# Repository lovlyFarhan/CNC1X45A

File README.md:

CNC1X45A
========

Stepper motor driver based on TB6600

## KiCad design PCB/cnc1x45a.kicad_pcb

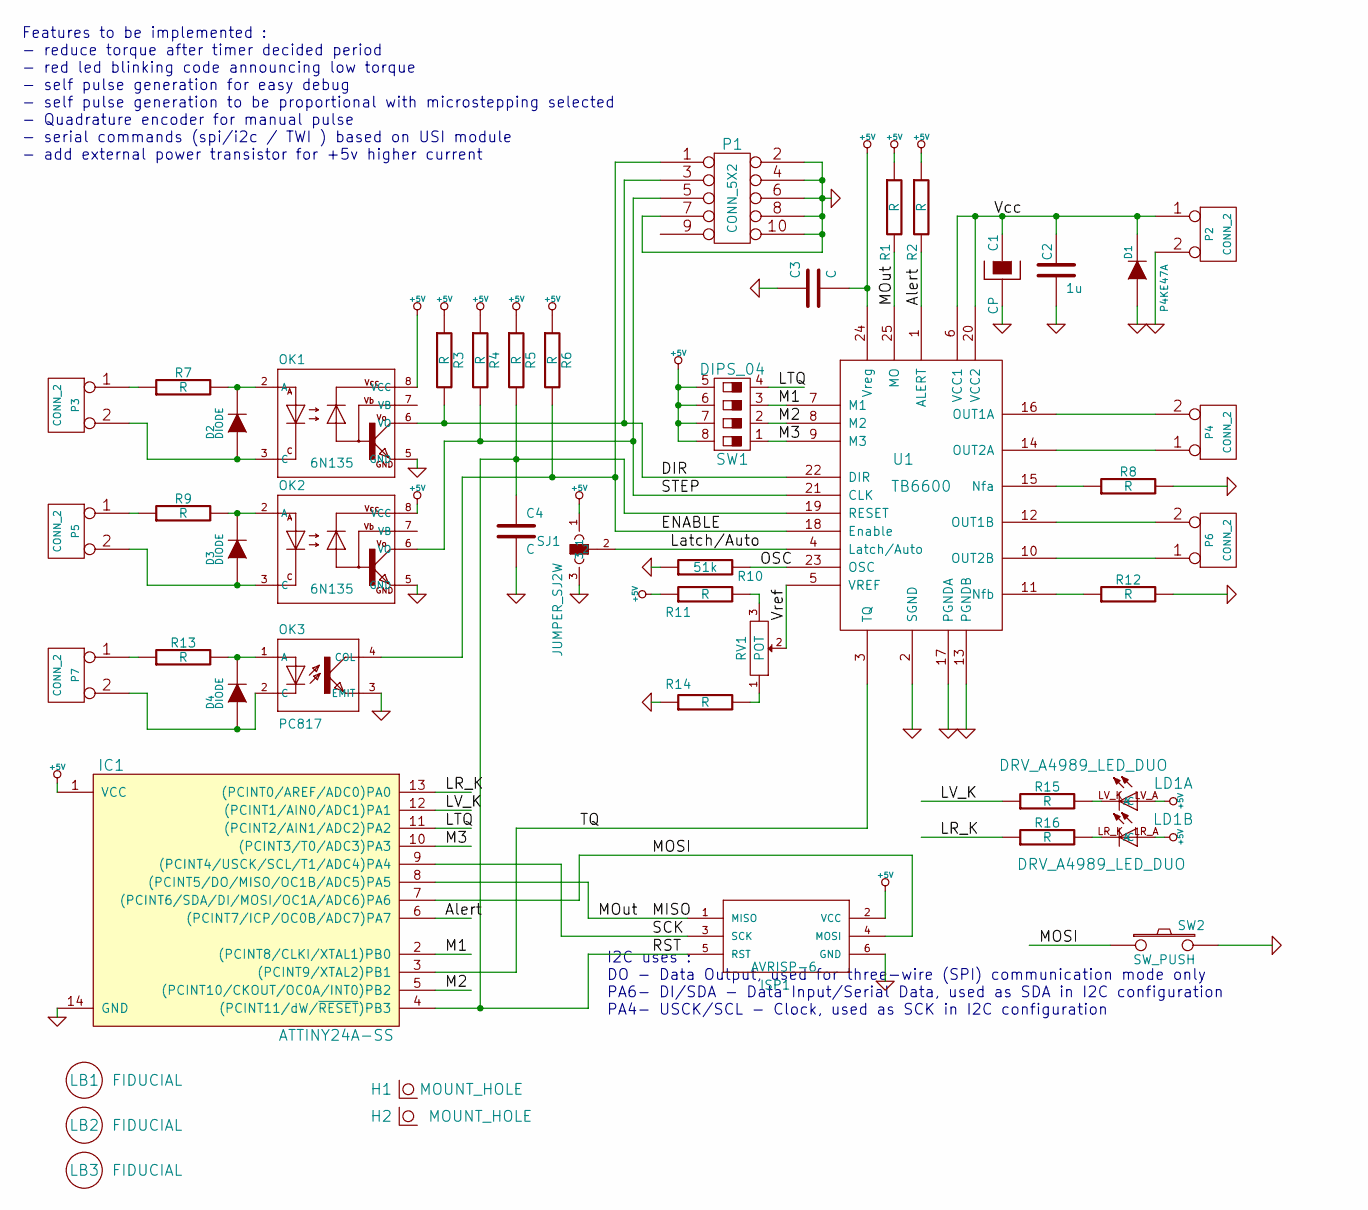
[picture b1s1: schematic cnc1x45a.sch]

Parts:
C1: CP
C2: 1u; SM1206
C3, C4: C
D1: P4KE47A
D2, D3, D4: DIODE
H1, H2: MOUNT_HOLE
IC1: ATTINY24A-SS; SO14
ISP1: AVRISP-6; adafruit-AVRISP
LB1, LB2, LB3: FIDUCIAL
LD1: DRV_A4989_LED_DUO
OK1, OK2: 6N135; optocoupler-2-DIL08
OK3: PC817; optocoupler-2-DIL04
P1: CONN_5X2
P2, P3, P4, P5, P6, P7: CONN_2
R1, R2, R3, R4, R5, R6, R7, R8, R9, R11, R12, R13, R14, R15, R16: R
R10: 51k
RV1: POT
SJ1: JUMPER_SJ2W; olimex-JUMPER_SJ_2
SW1: DIPS_04
SW2: SW_PUSH
U1: TB6600

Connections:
+5V: C3.2, IC1.1 (VCC), ISP1.2 (VCC), LD1.LR_A (A), LD1.LV_A (A), OK1.8 (VCC), OK2.8 (VCC), R1.1, R2.1, R3.1, R4.1, R5.1, R6.1, R11.1, SJ1.1, SW1.5, SW1.6, SW1.7, SW1.8, U1.24 (Vreg)
/Alert: IC1.6 ((PCINT7/ICP/OC0B/ADC7)PA7), R2.2, U1.1 (ALERT)
/DIR: OK1.6 (VO), P1.3, R3.2, U1.22 (DIR)
/ENABLE: OK3.4 (COL), P1.1, R6.2, U1.18 (Enable)
/LR_K: IC1.13 ((PCINT0/AREF/ADC0)PA0), R16.1
/LTQ: IC1.11 ((PCINT2/AIN1/ADC2)PA2), SW1.4
/LV_K: IC1.12 ((PCINT1/AIN0/ADC1)PA1), R15.1
/Latch/Auto: SJ1.2, U1.4 (Latch/Auto)
/M1: IC1.2 ((PCINT8/CLKI/XTAL1)PB0), SW1.3, U1.7 (M1)
/M2: IC1.5 ((PCINT10/CKOUT/OC0A/INT0)PB2), SW1.2, U1.8 (M2)
/M3: IC1.10 ((PCINT3/T0/ADC3)PA3), SW1.1, U1.9 (M3)
/MISO: IC1.8 ((PCINT5/DO/MISO/OC1B/ADC5)PA5), ISP1.1 (MISO), R1.2, U1.25 (MO)
/MOSI: IC1.7 ((PCINT6/SDA/DI/MOSI/OC1A/ADC6)PA6), ISP1.4 (MOSI), SW2.1
/OSC: R10.2, U1.23 (OSC)
/RST: C4.1, IC1.4 ((PCINT11/dW/~RESET~)PB3), ISP1.5 (RST), R5.2, U1.19 (RESET)
/SCK: IC1.9 ((PCINT4/USCK/SCL/T1/ADC4)PA4), ISP1.3 (SCK)
/STEP: OK2.6 (VO), P1.5, R4.2, U1.21 (CLK)
/TQ: IC1.3 ((PCINT9/XTAL2)PB1), U1.3 (TQ)
/Vcc: C1.1, C2.1, D1.2 (K), P2.1, U1.6 (VCC1), U1.20 (VCC2)
/Vref: RV1.2, U1.5 (VREF)
GND: C1.2, C2.2, C3.1, C4.2, D1.1 (A), IC1.14 (GND), ISP1.6 (GND), OK1.5 (GND), OK2.5 (GND), OK3.3 (EMIT), P1.2, P1.4, P1.6, P1.7, P1.8, P1.10, P2.2 (PM), R8.2, R10.1, R12.2, R14.1, SJ1.3, SW2.2, U1.2 (SGND), U1.13 (PGNDB), U1.17 (PGNDA)
unnamed: P5.1, R9.1
unnamed: D3.2 (K), OK2.2 (A), R9.2
unnamed: LD1.LR_K (C), R16.2
unnamed: LD1.LV_K (C), R15.2
unnamed: D3.1 (A), OK2.3 (C), P5.2 (PM)
unnamed: R14.2, RV1.1
unnamed: R11.2, RV1.3
unnamed: P6.1, U1.10 (OUT2B)
unnamed: P6.2 (PM), U1.12 (OUT1B)
unnamed: P4.1, U1.14 (OUT2A)
unnamed: P4.2 (PM), U1.16 (OUT1A)
unnamed: R12.1, U1.11 (Nfb)
unnamed: R8.1, U1.15 (Nfa)
unnamed: P3.1, R7.1
unnamed: D2.2 (K), OK1.2 (A), R7.2
unnamed: D2.1 (A), OK1.3 (C), P3.2 (PM)
unnamed: D4.1 (A), OK3.2 (C), P7.2 (PM)
unnamed: P7.1, R13.1
unnamed: D4.2 (K), OK3.1 (A), R13.2

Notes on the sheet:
Features to be implemented : - reduce torque after timer decided period - red led blinking code announcing low torque - self pulse generation for easy debug - self pulse generation to be proportional with microstepping selected - Quadrature encoder for manual pulse - serial commands (spi/i2c / TWI 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
I2C uses : DO - Data Output, used for three-wire (SPI) communication mode only PA6- DI/SDA - Data Input/Serial Data, used as SDA in I2C configuration PA4- USCK/SCL - Clock, used as SCK in I2C configuration

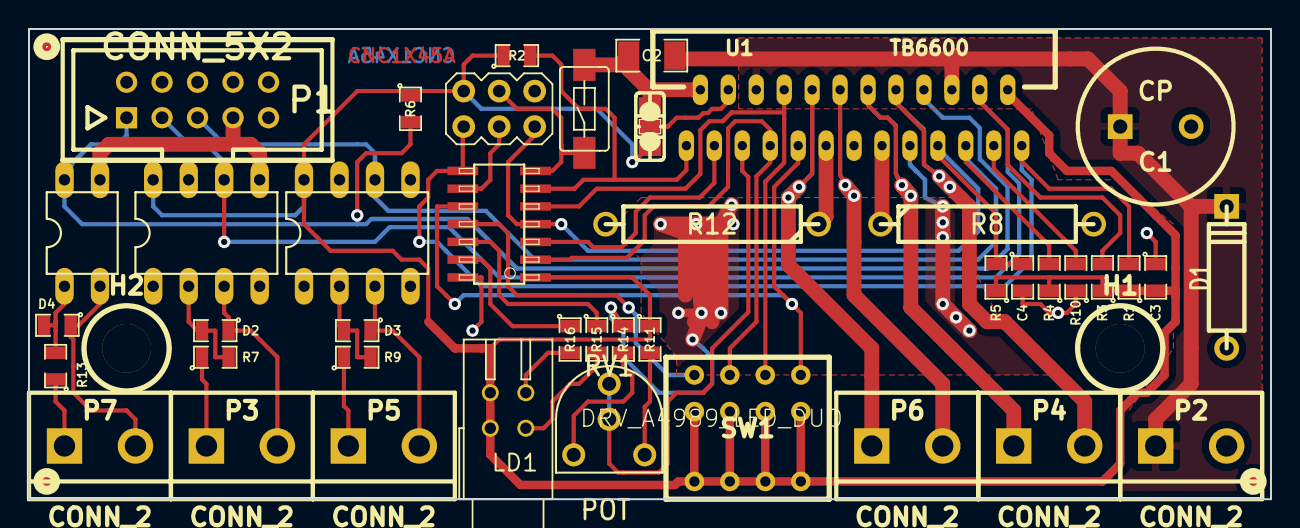
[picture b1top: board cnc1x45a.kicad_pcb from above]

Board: 2 copper layers, 88.9 x 33.7 mm, 47 parts (0 on the bottom side), 40 nets.

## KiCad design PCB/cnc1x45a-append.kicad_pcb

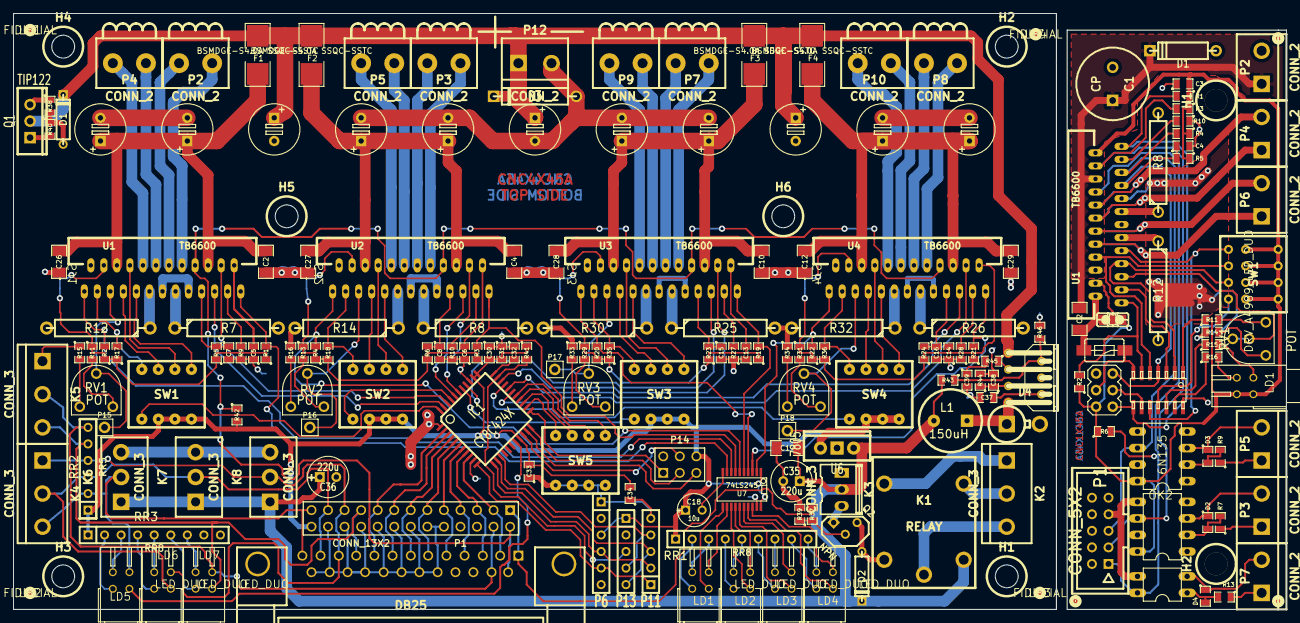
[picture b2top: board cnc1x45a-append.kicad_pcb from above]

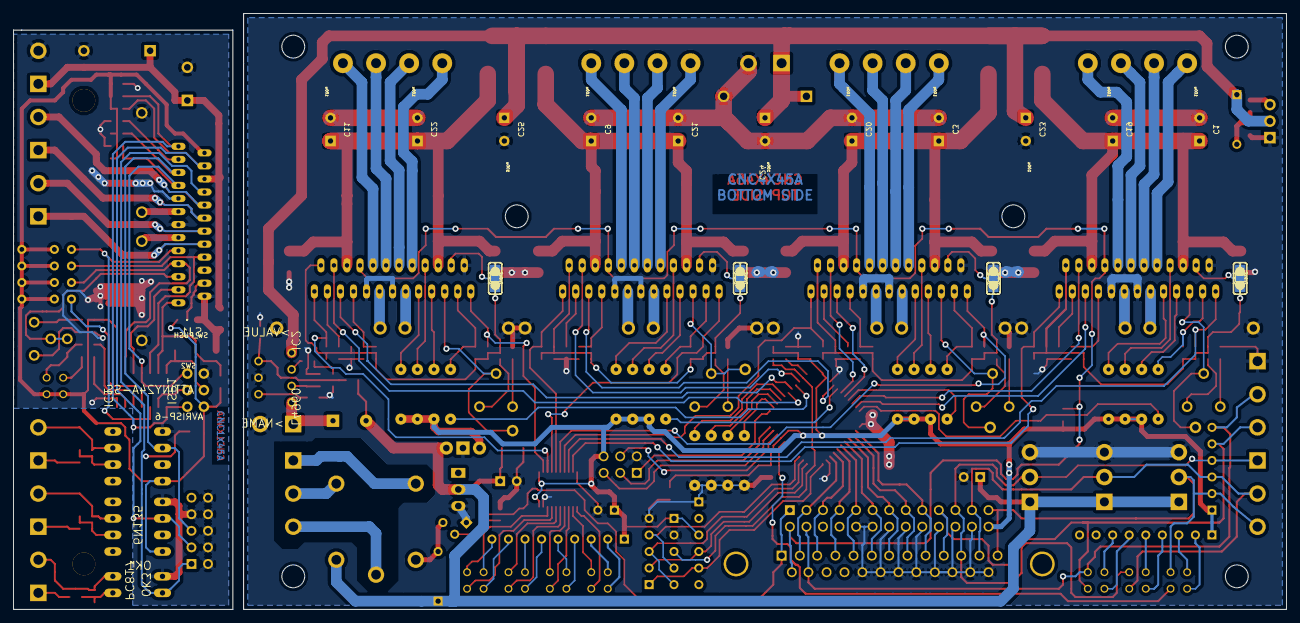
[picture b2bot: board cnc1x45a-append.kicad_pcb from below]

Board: 2 copper layers, 195.3 x 91.4 mm, 211 parts (4 on the bottom side), 185 nets.

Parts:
C1, C3, C9, C11, C19, C20, C21, C22, C23, C24, C25: 100u; CELEC_3.5MM_8MM
C1#2: CP; C2V10
C2, C2#2, C4, C10, C12, C17, C26, C27, C28, C29: 1u; SM1206
C3#2, C4#2, C5, C6, C13, C14: C; SM0805
C7, C8, C15, C16: 100n; SM0805
C18: 10u; C1V5
C30, C34: .1u; SM0805
C31, C32, C33: 1u; SM0805
C35, C36: 220u; C1V7
C37: 2.2uF; SM0805
C38: 2.2nF; SM0805
C39: 33nf; SM0805
D1: 39V; D3
D1#2: P4KE47A; D4
D2: DIODE; D3
D2#2, D3#2, D4#2: DIODE; SM0805
D3: Transil 1.5KE39; D5
D4: byw80 / STTH3R02; DO-201AD_Vertical_RM15
F1, F2, F3, F4: BSMDGE-S4.0A SSQC-SSTC; SSQC
H1, H1#2, H2, H2#2, H3, H4, H5, H6: MOUNT_HOLE; MountingHole_3-5mm_RevA_Date21Jun2010
IC1: CY8C424X; TQFP44
IC1#2: ATTINY24A-SS; SO14
IC2: L4960; l4960-HEPTAWATT
ISP1: AVRISP-6; adafruit-AVRISP
J1: DB25; DB25FC
K1: RELAY; LEG-XX
K2, K4, K5: CONN_3; bornier3
K3: CONN_3; kk100_22-23-2031
K6, K7, K8: CONN_3; bornier3_3.81
L1: 150uH; INDUCTOR_V
LB1, LB1#2, LB2, LB2#2, LB3, LB3#2, LB4: FIDUCIAL; olimex-SPARKFUNEAGLE-6-6-07_FIDUCIAL-1.5X3
LD1, LD2, LD3, LD4, LD5, LD6, LD7: LED_DUO
LD1#2: DRV_A4989_LED_DUO; LED_DUO
OK1, OK2: 6N135; optocoupler-2-DIL08
OK3: PC817; optocoupler-2-DIL04
P1: CONN_13X2; pin_array_13x2
P1#2: CONN_5X2; he10-10d-short
P2, P3, P4, P5, P7, P8, P9, P10: CONN_2; bornier2_Lsign
P2#2, P3#2, P4#2, P5#2, P6#2, P7#2, P12: CONN_2; bornier2
P6: CONN_6; SIL-6
P11, P13: CONN_5; SIL-5
P14: CONN_6; pin_array_3x2
P15, P16, P17, P18: CONN_1; PIN_ARRAY_1
Q1: TIP122; TO220_VERT
Q2: NPN; TO92
R1, R2, R3, R4, R9, R10, R10#2, R19, R20, R21, R22, R27, R28: 51k; SM0805
R1#2, R2#2, R3#2, R4#2, R5, R5#2, R6, R6#2, R7#2, R9#2, R11#2, R13#2, R14#2, R15#2, R16#2, R23, R24: R; SM0805
R7, R8, R12, R14, R25, R26, R30, R32: .20; R6_018
R8#2, R12#2: R; R6
R11, R13, R29, R31: 75k; SM0805
R15, R16, R33, R34: 8k06; SM0805
R17, R18, R35, R36: 10k; SM0805
R37, R40, R46: 4k7; SM0805
R38: 220; SM0805
R39: 100k; SM0805
R41: 24k; SM0805
R42: 20k; SM0805
R43: 6k2; SM0805
R44: 4k3; SM0805
R45: 15k; SM0805
RR1, RR3: RR8; r_pack8
RR2: RR5; r_pack5
RV1, RV2, RV3, RV4: POT; TRIM_POT
RV1#2: POT; RV2
SJ1, SJ1#2, SJ2, SJ3, SJ4: JUMPER_SJ2W; olimex-JUMPER_SJ_2
SW1, SW1#2, SW2, SW3, SW4, SW5: DIPS_04; DIPS-DS04
SW2#2: SW_PUSH; TACTILE-SWITCH-SMD-1101NE
U1, U1#2, U2, U3, U4: TB6600; HZIP25-P-1.00F
U6: 7805; 78XX_VERT
U7: 74LS245; SSOP20

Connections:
+5V: C3#2.2, C18.1, C30.2, C31.2, C33.2, C34.2, IC1.19, IC1.34, IC1.35, IC1#2.1, ISP1.2, LD1#2.LR_A, LD1#2.LV_A, OK1.8, OK2.8, P1.26, P6.3, P13.1, P14.6, R1#2.1, R2#2.1, R3#2.1, R4#2.1, R5#2.1, R6#2.1, R11#2.1, R41.1, R42.2, RR1.1, RR2.1, RR3.1, SJ1#2.1, SW1.6, SW1.7, SW1.8, SW1#2.5, SW1#2.6, SW1#2.7, SW1#2.8, SW2.6, SW2.7, SW2.8, SW3.6, SW3.7, SW3.8, SW4.6, SW4.7, SW4.8, U1#2.24, U6.VO, U7.1, U7.20
+12V: C17.1, C35.1, C36.1, D2.2, K1.B2, K3.2, K6.1, K7.1, K8.1, L1.2, R43.2, U6.VI
//XRES: IC1.32, P13.3, R41.2
/A-Alert: R22.2, U4.1, U7.2
/A-DIR: IC1.28, U4.22
/A-LTQ: IC1.30, SW4.5
/A-MOut: R21.2, U4.25, U7.3
/A-STEP: IC1.29, U4.21
/AVcc: C11.1, C12.1, C22.1, C29.2, F4.1, U4.6, U4.20
/Alert: IC1#2.6, R2#2.2, U1#2.1
/DIR: OK1.6, P1#2.3, R3#2.2, U1#2.22
/ENABLE: OK3.4, P1#2.1, R6#2.2, U1#2.18
/LR_K: IC1#2.13, R16#2.1
/LTQ: IC1#2.11, SW1#2.4
/LV_K: IC1#2.12, R15#2.1
/Latch/Auto: SJ1#2.2, U1#2.4
/M1: IC1#2.2, SW1#2.3, U1#2.7
/M2: IC1#2.5, SW1#2.2, U1#2.8
/M3: IC1#2.10, SW1#2.1, U1#2.9
/MISO: IC1#2.8, ISP1.1, R1#2.2, U1#2.25
/MOSI: IC1#2.7, ISP1.4, SW2#2.1
/OSC: R10#2.2, U1#2.23
/RST: C4#2.1, IC1#2.4, ISP1.5, R5#2.2, U1#2.19
/SCK: IC1#2.9, ISP1.3
/STEP: OK2.6, P1#2.5, R4#2.2, U1#2.21
/SWD CLK: IC1.14, P11.4, P13.4
/SWD IO: IC1.13, P11.3, P13.5
/TQ: IC1#2.3, U1#2.3
/V_Alim: C23.1, C24.1, C25.1, D1.2, D3.2, F1.2, F2.2, F3.2, F4.2, IC2.1, P12.1, Q1.3
/Vcc: C1#2.1, C2#2.1, D1#2.2, P2#2.1, U1#2.6, U1#2.20
/Vref: RV1#2.2, U1#2.5
/X-Alert: R2.2, U1.1, U7.8
/X-DIR: IC1.42, U1.22
/X-LTQ: IC1.44, SW1.5
/X-MOut: R1.2, U1.25, U7.9
/X-STEP: IC1.43, U1.21
/XVcc: C1.1, C2.1, C19.1, C26.2, F1.1, U1.6, U1.20
/Y-Alert: R4.2, U2.1, U7.6
/Y-DIR: IC1.39, U2.22
/Y-LTQ: IC1.41, SW2.5
/Y-MOut: R3.2, U2.25, U7.7
/Y-STEP: IC1.40, U2.21
/YVcc: C3.1, C4.1, C20.1, C27.2, F2.1, U2.6, U2.20
/Z-Alert: R20.2, U3.1, U7.4
/Z-DIR: IC1.31, U3.22
/Z-LTQ: IC1.38, SW3.5
/Z-MOut: R19.2, U3.25, U7.5
/Z-STEP: IC1.37, U3.21
/ZVcc: C9.1, C10.1, C21.1, C28.2, F3.1, U3.6, U3.20
/a_min: J1.10, K5.3, LD7.LV_K, P1.19, RR2.5
/blink: IC1.18, LD5.LV_K
/clka: IC1.2, J1.9, P1.17
/clkx: IC1.8, J1.3, P1.5
/clky: IC1.6, J1.5, P1.9
/clkz: IC1.4, J1.7, P1.13
/dira: IC1.3, J1.8, P1.15
/dirx: IC1.9, J1.2, P1.3
/diry: IC1.7, J1.4, P1.7
/dirz: IC1.5, J1.6, P1.11
/e_stop: J1.15, K5.2, LD7.LR_K, P1.4, RR2.6
/ena: J1.14, P1.2, R42.1, U1.18, U2.18, U3.18, U4.18
/spindle: J1.1, P1.1, R37.1
/x_min: J1.13, K4.3, K6.2, LD5.LR_K, P1.25, RR2.2
/y_min: J1.12, K4.2, K7.2, LD6.LV_K, P1.23, RR2.3
/z_min: J1.11, K4.1, K8.2, LD6.LR_K, P1.21, RR2.4
GND: C1.2, C1#2.2, C2.2, C2#2.2, C3.2, C3#2.1, C4.2, C4#2.2, C5.1, C6.1, C7.2, C8.2, C9.2, C10.2, C11.2, C12.2, C13.1, C14.1, C15.2, C16.2, C17.2, C18.2, C19.2, C20.2, C21.2, C22.2, C23.2, C24.2, C25.2, C26.1, C27.1, C28.1, C29.1, C30.1, C31.1, C32.1, C33.1, C34.1, C35.2, C36.2, C37.2, C38.2, C39.2, D1#2.1, D3.1, D4.1, IC1.1, IC1.10, IC1.36, IC1#2.14, IC2.4, ISP1.6, J1.18, J1.19, J1.20, J1.21, J1.22, J1.23, J1.24, J1.25, K3.3, K5.1, K6.3, K7.3, K8.3, OK1.5, OK2.5, OK3.3, P1.10, P1.12, P1.14, P1.16, P1.18, P1.20, P1.22, P1.24, P1#2.2, P1#2.4, P1#2.6, P1#2.7, P1#2.8, P1#2.10, P2#2.2, P6.1, P11.5, P12.2, P13.2, P14.2, Q1.1, Q2.1, R7.2, R8.2, R8#2.2, R9.1, R10.1, R10#2.1, R12.2, R12#2.2, R14.2, R14#2.1, R15.1, R16.1, R25.2, R26.2, R27.1, R28.1, R30.2, R32.2, R33.1, R34.1, R39.2, R40.2, R44.2, R46.2, SJ1.3, SJ1#2.3, SJ2.3, SJ3.3, SJ4.3, SW2#2.2, SW5.5, SW5.6, SW5.7, SW5.8, U1.2, U1.13, U1.17, U1#2.2, U1#2.13, U1#2.17, U2.2, U2.13, U2.17, U3.2, U3.13, U3.17, U4.2, U4.13, U4.17, U6.GND, U7.10, U7.19
unnamed: Q2.2, R37.2, R39.1
unnamed: D2.1, K1.B1, Q2.3
unnamed: D1.1, R38.2, R40.1
unnamed: P5#2.1, R9#2.1
unnamed: D3#2.2, OK2.2, R9#2.2
unnamed: LD1#2.LR_K, R16#2.2
unnamed: LD1#2.LV_K, R15#2.2
unnamed: Q1.2, R38.1
unnamed: LD3.LR_A, RR1.7
unnamed: LD1.LR_A, RR1.3
unnamed: LD1.LV_A, RR1.2
unnamed: LD4.LV_A, RR1.8
unnamed: LD4.LR_A, RR1.9
unnamed: LD3.LV_K, U7.15
unnamed: LD3.LV_A, RR1.6
unnamed: LD2.LR_A, RR1.5
unnamed: LD2.LV_K, U7.13
unnamed: LD2.LV_A, RR1.4
unnamed: IC1.24, SW5.4
unnamed: IC1.25, SW5.3
unnamed: D3#2.1, IC1.26, OK2.3, P5#2.2, SW5.2
unnamed: R14#2.2, RV1#2.1
unnamed: R11#2.2, RV1#2.3
unnamed: P6#2.1, U1#2.10
unnamed: P6#2.2, U1#2.12
unnamed: K1.NA, K2.2, P4#2.1, U1#2.14
unnamed: K1.C, K2.3, P4#2.2, U1#2.16
unnamed: K1.NF, K2.1, R12#2.1, U1#2.11
unnamed: R8#2.1, U1#2.15
unnamed: SW4.3, U4.7
unnamed: SW4.2, U4.8
unnamed: P3#2.1, R7#2.1, SW4.1, U4.9
unnamed: D2#2.2, OK1.2, P10.1, R7#2.2, U4.10
unnamed: D2#2.1, OK1.3, P3#2.2, P10.2, U4.12
unnamed: P8.1, U4.14
unnamed: D4#2.1, OK3.2, P7#2.2, P8.2, U4.16
unnamed: P7#2.1, R13#2.1, R32.1, U4.11
unnamed: D4#2.2, OK3.1, R13#2.2, R26.1, U4.15
unnamed: P18.1, RV4.2, U4.5
unnamed: R28.2, U4.23
unnamed: R31.2, RV4.3
unnamed: R34.2, RV4.1
unnamed: R36.2, SW4.4, U4.3
unnamed: LD4.LR_K, U7.18
unnamed: LD4.LV_K, U7.17
unnamed: LD3.LR_K, U7.16
unnamed: LD2.LR_K, U7.14
unnamed: LD1.LR_K, U7.12
unnamed: LD1.LV_K, U7.11
unnamed: IC1.27, SW5.1
unnamed: IC1.11, P6.5, P11.1
unnamed: C16.1, R24.2, U4.19
unnamed: R33.2, RV3.1
unnamed: R16.2, RV2.1
unnamed: R15.2, RV1.1
unnamed: C14.2, R21.1, R22.1, R24.1, R31.1, R36.1, SJ4.1, SJ4.2, U4.4, U4.24
unnamed: C32.2, IC1.33
unnamed: IC2.3, R45.1
unnamed: IC1.21, P14.5
unnamed: IC1.20, P14.4
unnamed: IC1.23, P14.1
unnamed: IC2.2, R43.1, R46.1
unnamed: IC1.22, P14.3
unnamed: C38.1, IC2.5, R44.1
unnamed: C37.1, IC2.6
unnamed: D4.2, IC2.7, L1.1
unnamed: C39.1, R45.2
unnamed: LD7.LR_A, RR3.7
unnamed: LD7.LV_A, RR3.6
unnamed: LD6.LR_A, RR3.5
unnamed: LD5.LR_A, RR3.3
unnamed: LD6.LV_A, RR3.4
unnamed: LD5.LV_A, RR3.2
unnamed: P2.2, U1.16
unnamed: R11.2, RV1.3
unnamed: R7.1, U1.15
unnamed: P2.1, U1.14
unnamed: R9.2, U1.23
unnamed: P4.2, U1.12
unnamed: R12.1, U1.11
unnamed: P4.1, U1.10
unnamed: SW1.1, U1.9
unnamed: SW1.2, U1.8
unnamed: SW1.3, U1.7
unnamed: P15.1, RV1.2, U1.5
unnamed: IC1.12, P6.4, P11.2
unnamed: R17.2, SW1.4, U1.3
unnamed: C5.2, R1.1, R2.1, R5.1, R11.1, R17.1, SJ1.1, SJ1.2, U1.4, U1.24
unnamed: C7.1, R5.2, U1.19
unnamed: R27.2, U3.23
unnamed: C13.2, R19.1, R20.1, R23.1, R29.1, R35.1, SJ3.1, SJ3.2, U3.4, U3.24
unnamed: SW3.3, U3.7
unnamed: SW3.2, U3.8
unnamed: SW3.1, U3.9
unnamed: P9.1, U3.10
unnamed: P9.2, U3.12
unnamed: P7.1, U3.14
unnamed: P7.2, U3.16
unnamed: R30.1, U3.11
unnamed: R25.1, U3.15
unnamed: R29.2, RV3.3
unnamed: P17.1, RV3.2, U3.5
unnamed: R35.2, SW3.4, U3.3
unnamed: C15.1, R23.2, U3.19
unnamed: R13.2, RV2.3
unnamed: C6.2, R3.1, R4.1, R6.1, R13.1, R18.1, SJ2.1, SJ2.2, U2.4, U2.24
unnamed: R18.2, SW2.4, U2.3
unnamed: P16.1, RV2.2, U2.5
unnamed: R10.2, U2.23
unnamed: SW2.2, U2.8
unnamed: SW2.3, U2.7
unnamed: SW2.1, U2.9
unnamed: R14.1, U2.11
unnamed: P5.2, U2.12
unnamed: P5.1, U2.10
unnamed: P3.1, U2.14
unnamed: P3.2, U2.16
unnamed: R8.1, U2.15
unnamed: C8.1, R6.2, U2.19

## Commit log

2014-08-14 Initial version
    PCB folder is complete. SW / firmware will follow
